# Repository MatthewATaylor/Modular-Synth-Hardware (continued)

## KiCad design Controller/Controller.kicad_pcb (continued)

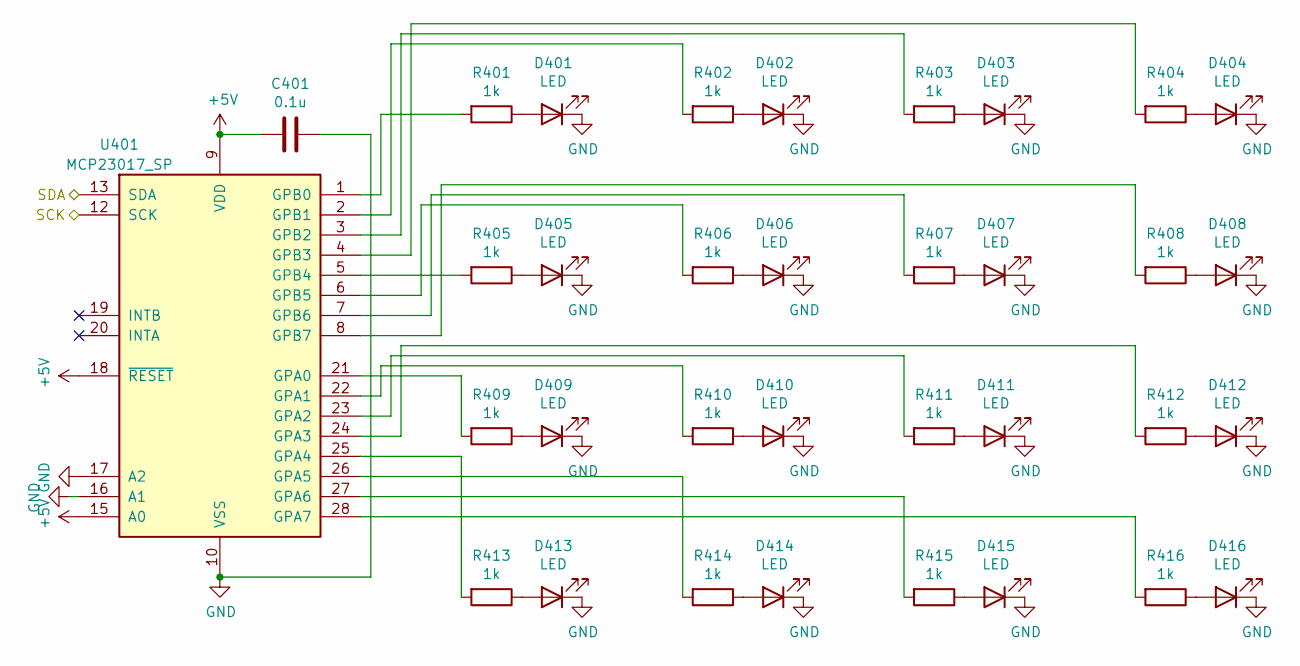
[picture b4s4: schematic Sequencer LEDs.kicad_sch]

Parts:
C401: 0.1u; C_Disc_D5.0mm_W2.5mm_P5.00mm
D401, D402, D403, D404, D405, D406, D407, D408, D409, D410, D411, D412, D413, D414, D415, D416: LED; LED_D5.0mm
R401, R402, R403, R404, R405, R406, R407, R408, R409, R410, R411, R412, R413, R414, R415, R416: 1k; R_Axial_DIN0207_L6.3mm_D2.5mm_P7.62mm_Horizontal
U401: MCP23017_SP; DIP-28_W7.62mm_Socket

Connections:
+5V: C401.2, U401.9 (VDD), U401.15 (A0), U401.18 (~RESET); also elsewhere on the board
/Out/SCK: U401.12 (SCK); also elsewhere on the board
/Out/SDA: U401.13 (SDA); also elsewhere on the board
GND: C401.1, D401.1 (K), D402.1 (K), D403.1 (K), D404.1 (K), D405.1 (K), D406.1 (K), D407.1 (K), D408.1 (K), D409.1 (K), D410.1 (K), D411.1 (K), D412.1 (K), D413.1 (K), D414.1 (K), D415.1 (K), D416.1 (K), U401.10 (VSS), U401.16 (A1), U401.17 (A2); also elsewhere on the board
unnamed: D401.2 (A), R401.1
unnamed: D402.2 (A), R402.1
unnamed: D403.2 (A), R403.1
unnamed: D404.2 (A), R404.1
unnamed: D405.2 (A), R405.1
unnamed: D406.2 (A), R406.1
unnamed: D407.2 (A), R407.1
unnamed: D408.2 (A), R408.1
unnamed: D409.2 (A), R409.1
unnamed: D410.2 (A), R410.1
unnamed: D411.2 (A), R411.1
unnamed: D412.2 (A), R412.1
unnamed: D413.2 (A), R413.1
unnamed: D414.2 (A), R414.1
unnamed: D415.2 (A), R415.1
unnamed: D416.2 (A), R416.1
unnamed: R401.2, U401.1 (GPB0)
unnamed: R402.2, U401.2 (GPB1)
unnamed: R403.2, U401.3 (GPB2)
unnamed: R404.2, U401.4 (GPB3)
unnamed: R405.2, U401.5 (GPB4)
unnamed: R406.2, U401.6 (GPB5)
unnamed: R407.2, U401.7 (GPB6)
unnamed: R408.2, U401.8 (GPB7)
unnamed: R409.2, U401.21 (GPA0)
unnamed: R410.2, U401.22 (GPA1)
unnamed: R411.2, U401.23 (GPA2)
unnamed: R412.2, U401.24 (GPA3)
unnamed: R413.2, U401.25 (GPA4)
unnamed: R414.2, U401.26 (GPA5)
unnamed: R415.2, U401.27 (GPA6)
unnamed: R416.2, U401.28 (GPA7)

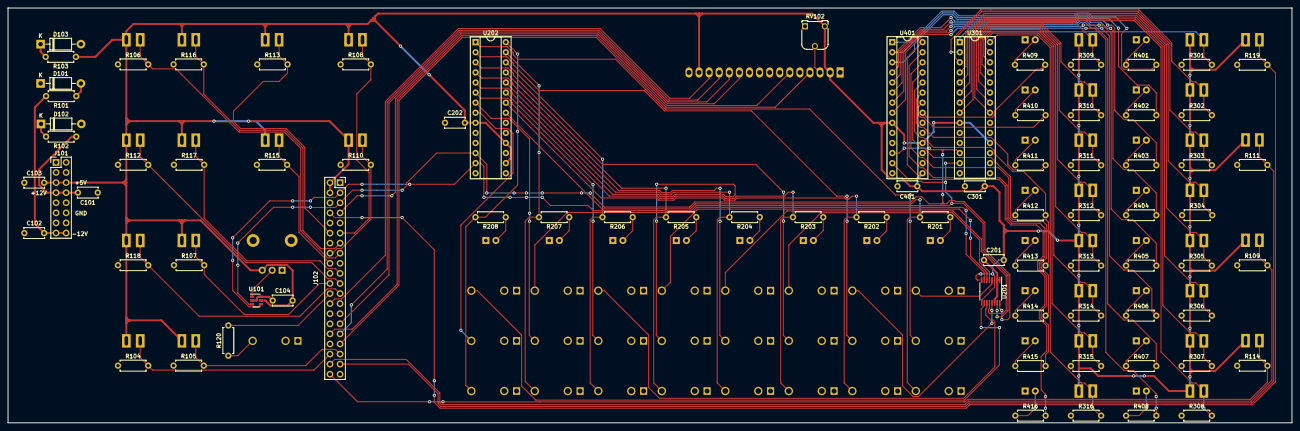
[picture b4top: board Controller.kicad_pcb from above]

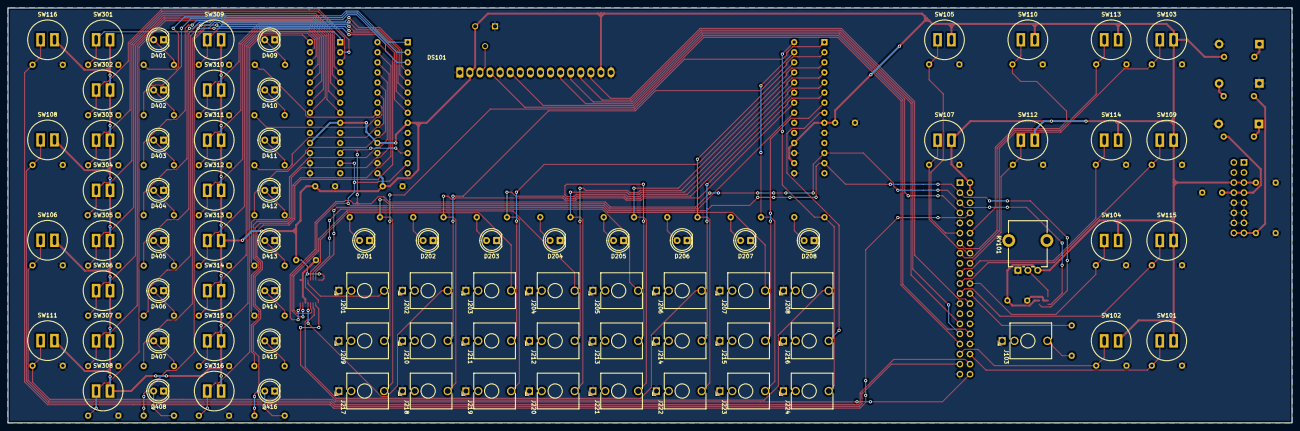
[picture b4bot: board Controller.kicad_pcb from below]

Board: 2 copper layers, 323.5 x 104.5 mm, 162 parts (83 on the bottom side), 115 nets.
